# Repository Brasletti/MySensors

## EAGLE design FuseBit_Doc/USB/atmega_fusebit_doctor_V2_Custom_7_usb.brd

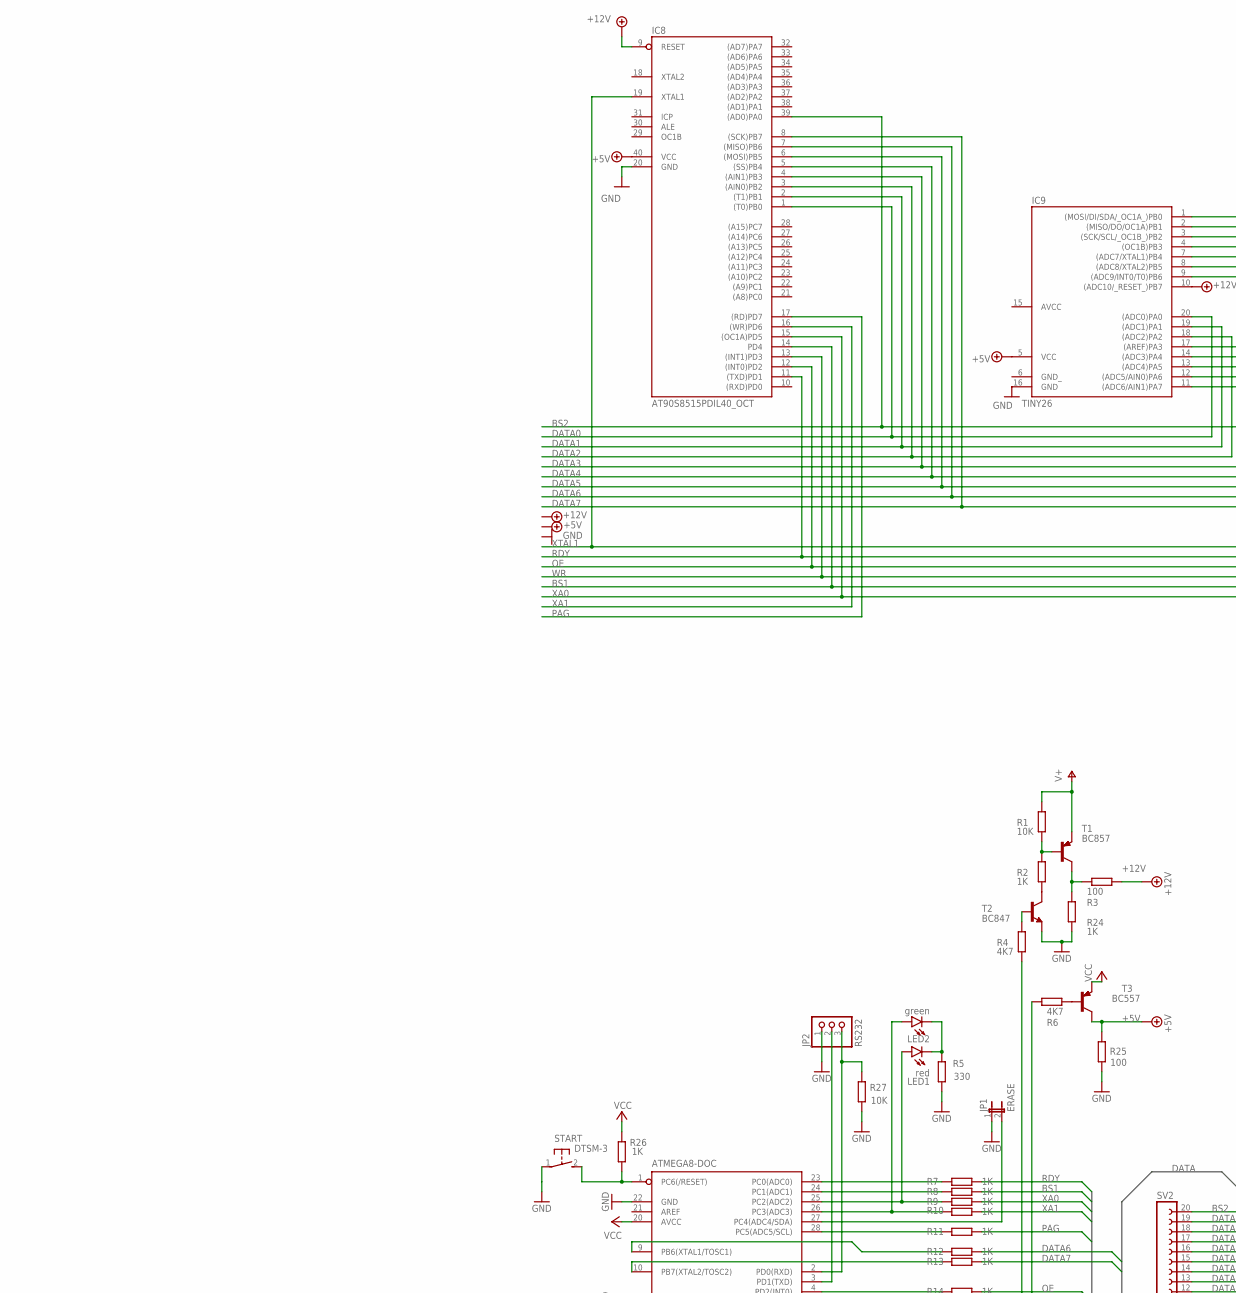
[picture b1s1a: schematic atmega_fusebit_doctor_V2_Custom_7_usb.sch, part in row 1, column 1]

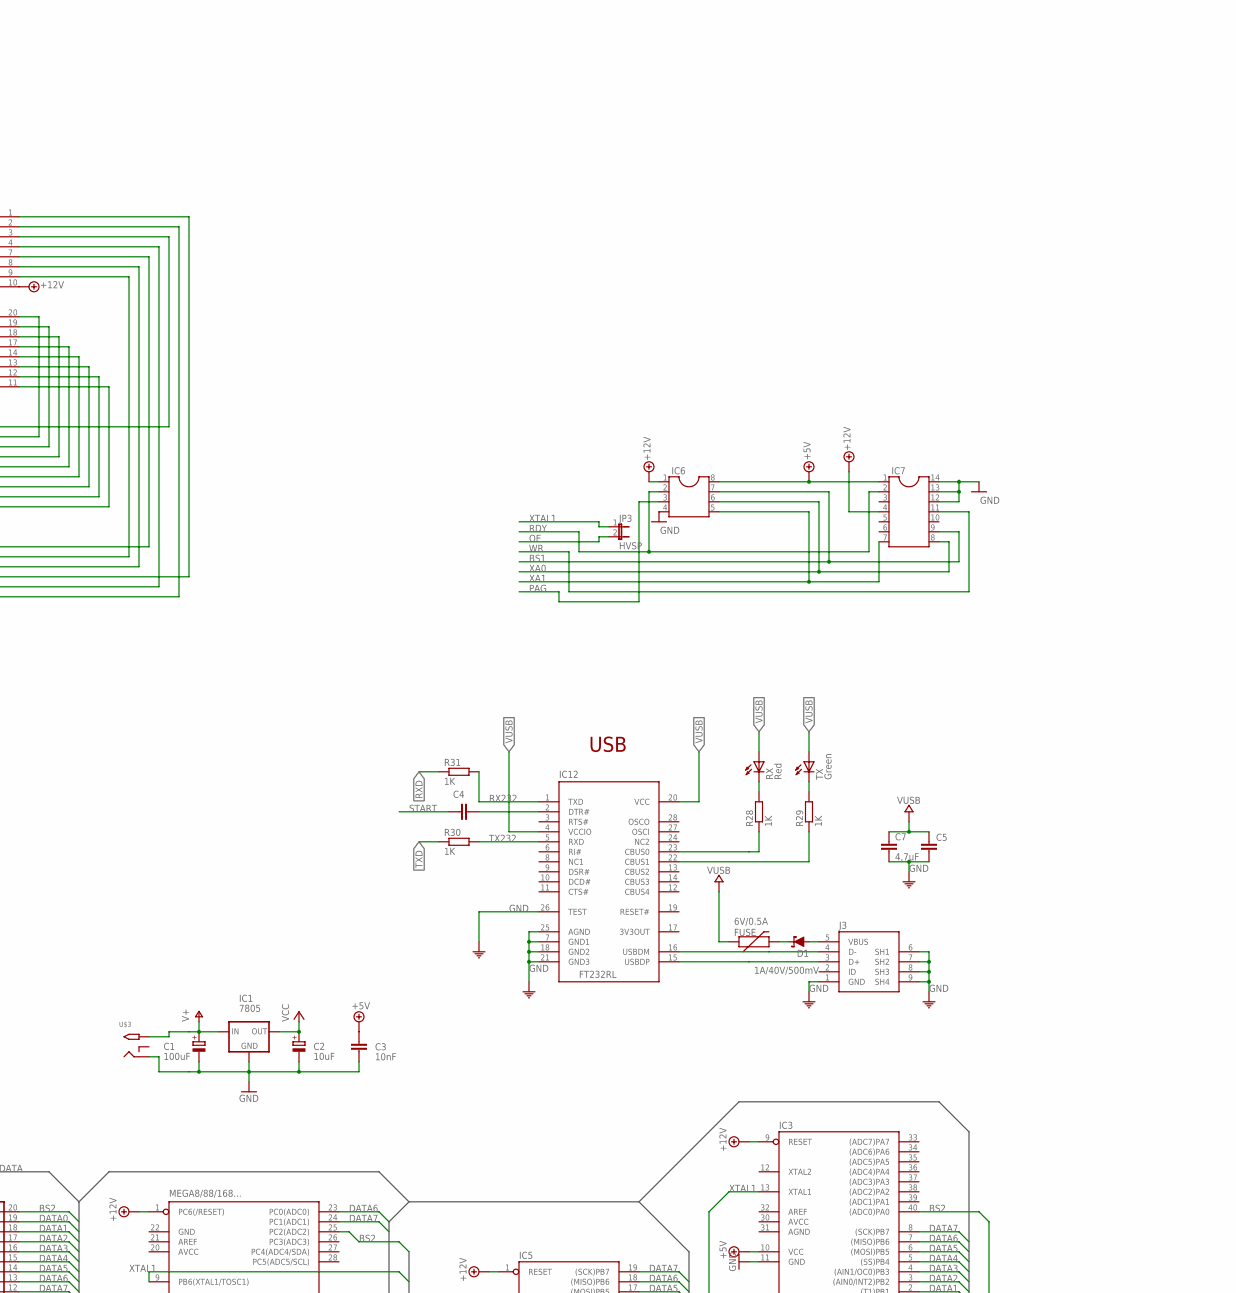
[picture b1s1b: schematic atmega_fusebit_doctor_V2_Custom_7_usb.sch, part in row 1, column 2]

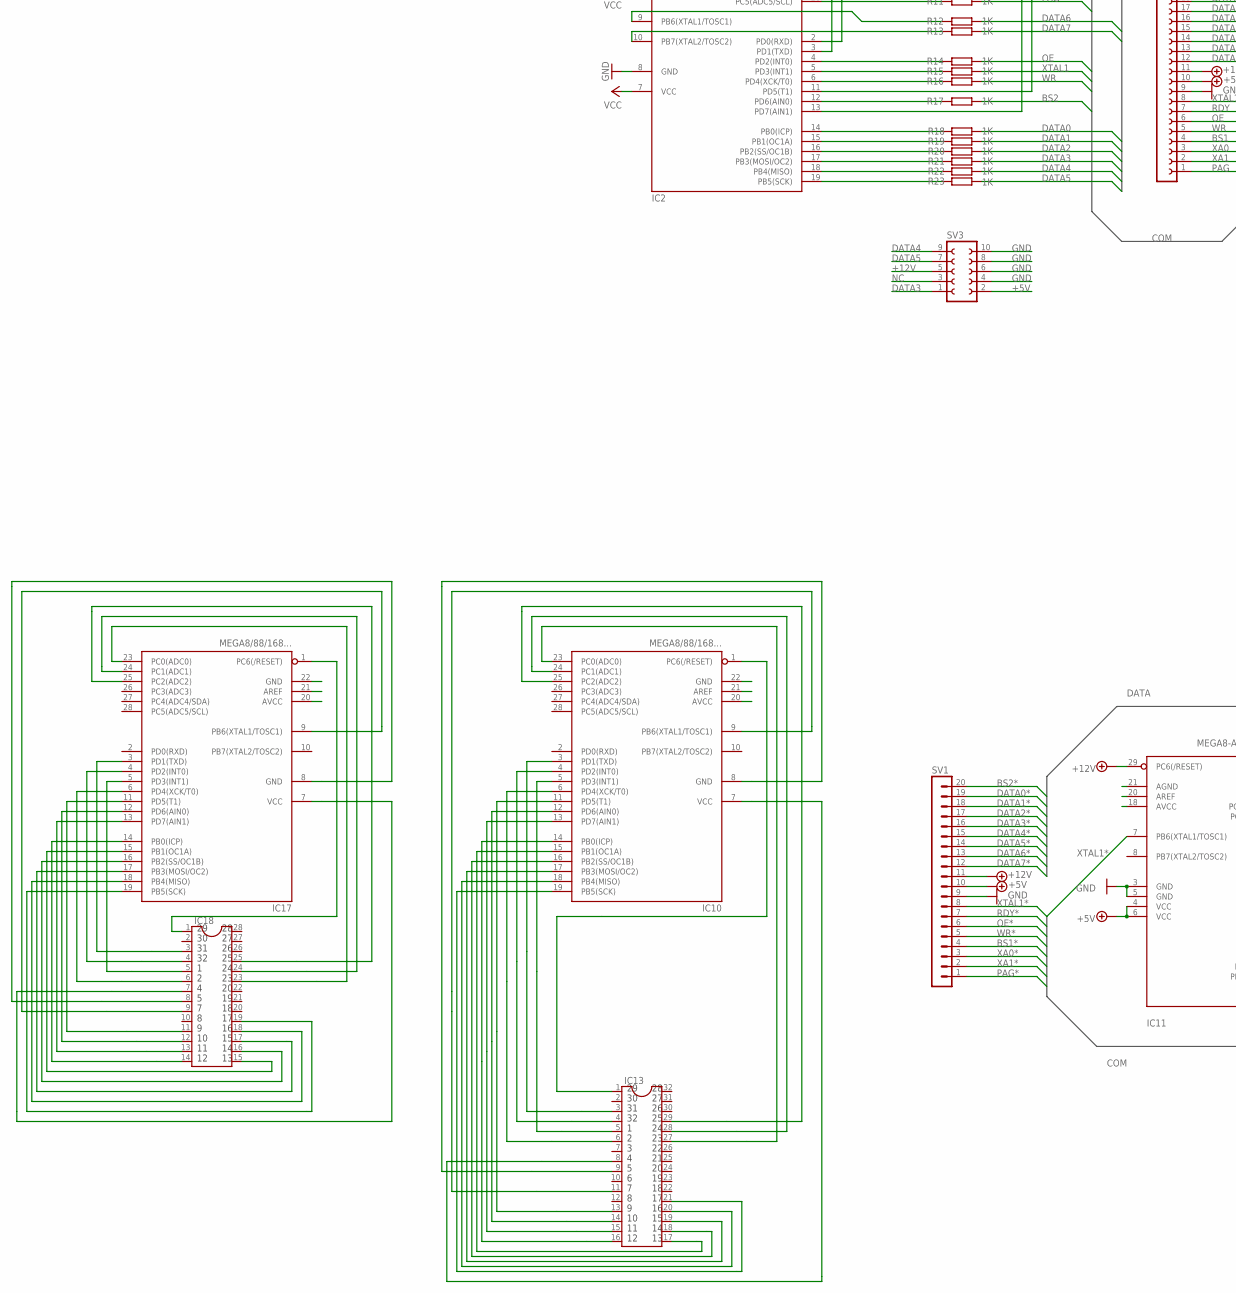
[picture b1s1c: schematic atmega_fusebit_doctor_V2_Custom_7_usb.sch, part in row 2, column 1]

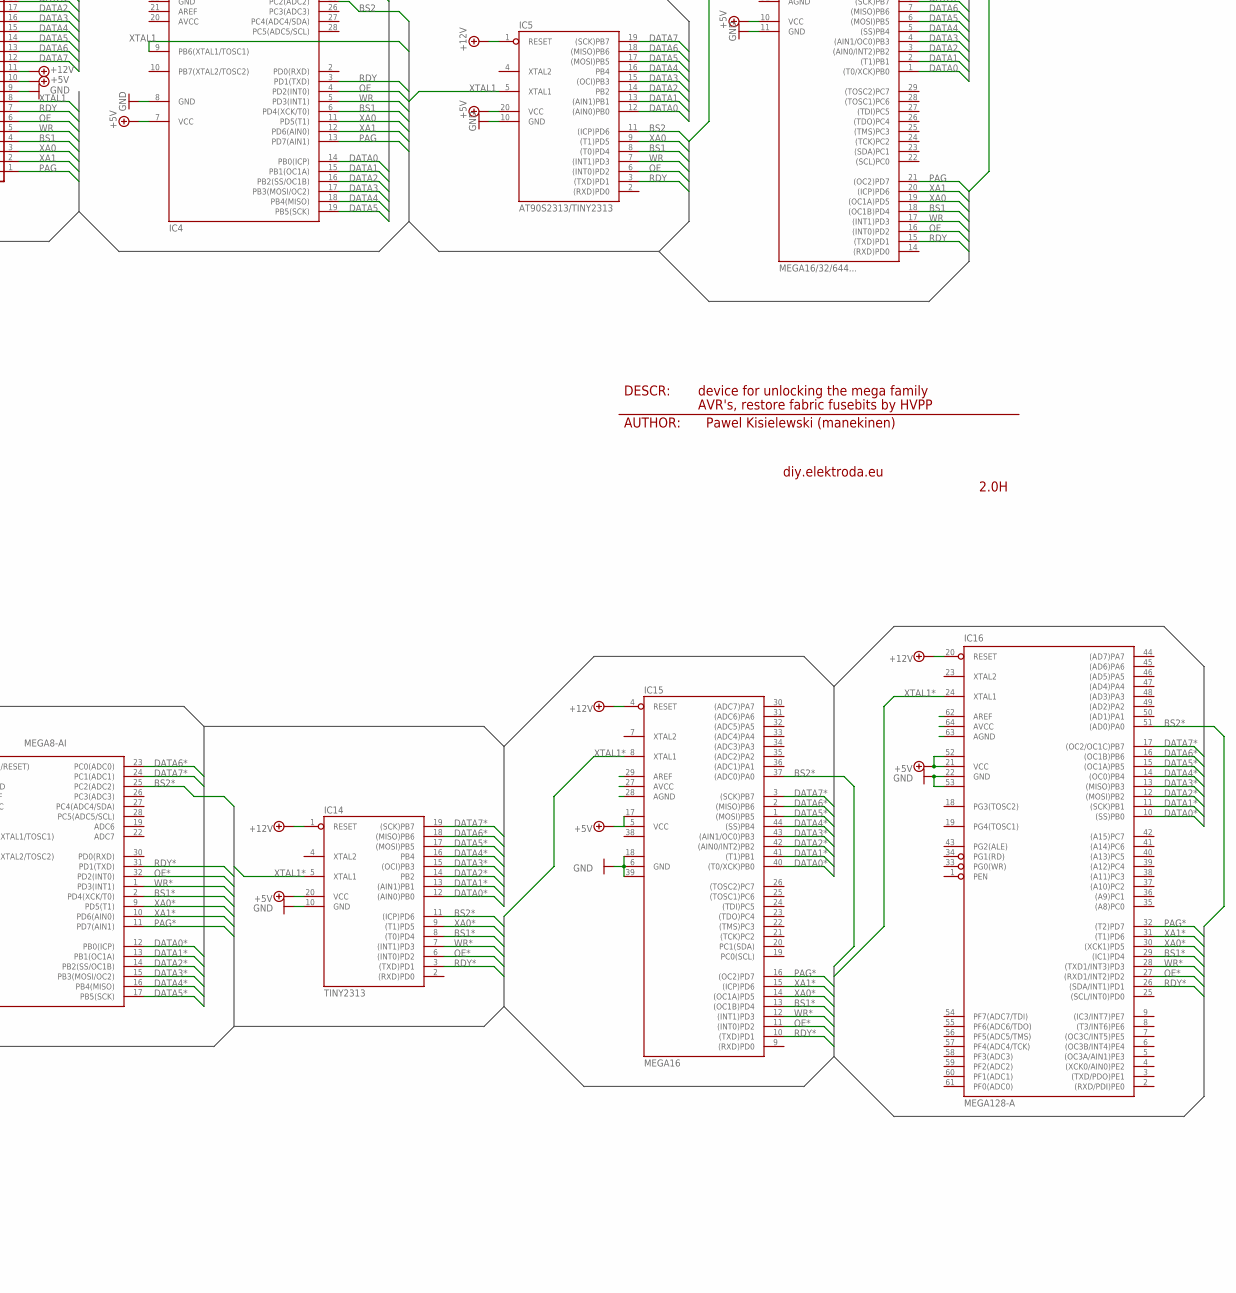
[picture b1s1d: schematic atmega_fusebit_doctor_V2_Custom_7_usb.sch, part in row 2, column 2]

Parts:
C1: 100uF; 153CLV-0605
C2: 10uF; 153CLV-0405
C3: 10nF; C0805
C4, C5: 100nF; C0805
C7: 4,7uF; C1206
D1: 1A/40V/500mV; SMA-DIODE
FUSE: 6V/0.5A; 1206
IC1: 7805; 78XXL
IC2: ATMEGA8-DOC; DIL28-3_OCT
IC3: MEGA16/32/644...; DIL40_OCT
IC4, IC10, IC17: MEGA8/88/168...; DIL28-3_OCT
IC5: AT90S2313/TINY2313; DIL20_OCT
IC6: DIL8S; SOCKED-08
IC7: DIL14S; SOCKED-14
IC8: AT90S8515PDIL40_OCT; DIL40_OCT
IC9: TINY26; DIL20_OCT
IC11: MEGA8-AI; TQFP32-08
IC12: FT232RL; SSOP28
IC13: DIL32
IC14: TINY2313; SO20L
IC15: MEGA16; TQFP44
IC16: MEGA128-A; TQFP64
IC18: DIL28; DIL28-6
J3: 0219_14850; USB-MINI-B_2
JP1: ERASE; JP1
JP2: RS232; 1X03
JP3: HVSP; JP1
LED1: red; LED-1206
LED2: green; LED-1206
R1, R27: 10K; R0805
R2, R7, R8, R9, R10, R11, R12, R13, R14, R15, R16, R17, R18, R19, R20, R21, R22, R23, R24, R26, R28, R29, R30, R31: 1K; R0805
R3, R25: 100; R0805
R4, R6: 4K7; R0805
R5: 330; R0805
RX: Red; CHIPLED_0805
START: DTSM-3
SV1: MA20-1
SV2: FE20-1; FE20
SV3: FE05-2
T1: BC857; SOT23-BEC
T2: BC847; SOT23
T3: BC557; SOT23-BEC
TX: Green; CHIPLED_0805
U$3: 2.1MMJACKTHM; PJ-102A

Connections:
1: IC10.5 (PD3(INT1)), IC13.5
2: IC10.6 (PD4(XCK/T0)), IC13.6
3: IC17.1 (PC6(/RESET)), IC18.1
3V3OUT: IC12.17 (3V3OUT)
4: IC10.7 (VCC), IC13.8
5: IC10.8 (GND), IC13.9
7: IC10.9 (PB6(XTAL1/TOSC1)), IC13.11
9: IC10.11 (PD5(T1)), IC13.13
10: IC10.12 (PD6(AIN0)), IC13.14
11: IC10.13 (PD7(AIN1)), IC13.15
12: IC10.14 (PB0(ICP)), IC13.16
13: IC10.15 (PB1(OC1A)), IC13.17
14: IC10.16 (PB2(SS/OC1B)), IC13.18
15: IC10.17 (PB3(MOSI/OC2)), IC13.19
16: IC10.18 (PB4(MISO)), IC13.20
17: IC10.19 (PB5(SCK)), IC13.21
19: IC17.3 (PD1(TXD)), IC18.3
20: IC17.4 (PD2(INT0)), IC18.4
21: IC17.5 (PD3(INT1)), IC18.5
22: IC17.6 (PD4(XCK/T0)), IC18.6
23: IC10.23 (PC0(ADC0)), IC13.27
24: IC10.24 (PC1(ADC1)), IC13.28
25: IC10.25 (PC2(ADC2)), IC13.29
29: IC10.1 (PC6(/RESET)), IC13.1
31: IC10.3 (PD1(TXD)), IC13.3
32: IC10.4 (PD2(INT0)), IC13.4
33: IC17.7 (VCC), IC18.7
34: IC17.8 (GND), IC18.8
35: IC17.9 (PB6(XTAL1/TOSC1)), IC18.9
37: IC17.11 (PD5(T1)), IC18.11
38: IC17.12 (PD6(AIN0)), IC18.12
39: IC17.13 (PD7(AIN1)), IC18.13
40: IC17.14 (PB0(ICP)), IC18.14
41: IC17.15 (PB1(OC1A)), IC18.15
42: IC17.16 (PB2(SS/OC1B)), IC18.16
43: IC17.17 (PB3(MOSI/OC2)), IC18.17
44: IC17.18 (PB4(MISO)), IC18.18
45: IC17.19 (PB5(SCK)), IC18.19
47: IC17.23 (PC0(ADC0)), IC18.23
48: IC17.24 (PC1(ADC1)), IC18.24
49: IC17.25 (PC2(ADC2)), IC18.25
+5V: C3.1, IC3.10 (VCC), IC4.7 (VCC), IC5.20 (VCC), IC6.8, IC7.1, IC8.40 (VCC), IC9.5 (VCC), R25.2, SV2.10, SV3.2, T3.C
+5V*: IC11.4 (VCC), IC11.6 (VCC), IC14.20 (VCC), IC15.5 (VCC), IC15.17 (VCC1), IC16.21 (VCC), IC16.52 (VCC1), SV1.10
+12V: IC3.9 (RESET), IC4.1 (PC6(/RESET)), IC5.1 (RESET), IC6.1, IC7.4, IC8.9 (RESET), IC9.10 ((ADC10/_RESET_)PB7), R3.2, SV2.11, SV3.5
+12V*: IC11.29 (PC6(/RESET)), IC14.1 (RESET), IC15.4 (RESET), IC16.20 (RESET), SV1.11
AGND: IC3.31 (AGND)
AREF: IC3.32 (AREF)
AVCC: IC3.30 (AVCC), IC4.20 (AVCC), IC9.15 (AVCC)
BS1: IC3.18 ((OC1B)PD4), IC4.6 (PD4(XCK/T0)), IC5.8 ((T0)PD4), IC6.7, IC7.9, IC8.14 (PD4), IC9.4 ((OC1B)PB3), R8.2, SV2.4
BS1*: IC11.2 (PD4(XCK/T0)), IC14.8 ((T0)PD4), IC15.13 ((OC1B)PD4), IC16.29 ((IC1)PD4), SV1.4
BS2: IC3.40 ((ADC0)PA0), IC4.25 (PC2(ADC2)), IC5.11 ((ICP)PD6), IC8.39 ((AD0)PA0), IC9.3 ((SCK/SCL/_OC1B_)PB2), R17.2, SV2.20
BS2*: IC11.25 (PC2(ADC2)), IC14.11 ((ICP)PD6), IC15.37 ((ADC0)PA0), IC16.51 ((AD0)PA0), SV1.20
DATA0: IC3.1 ((T0/XCK)PB0), IC4.14 (PB0(ICP)), IC5.12 ((AIN0)PB0), IC8.1 ((T0)PB0), IC9.20 ((ADC0)PA0), R18.2, SV2.19
DATA0*: IC11.12 (PB0(ICP)), IC14.12 ((AIN0)PB0), IC15.40 ((T0/XCK)PB0), IC16.10 ((SS)PB0), SV1.19
DATA1: IC3.2 ((T1)PB1), IC4.15 (PB1(OC1A)), IC5.13 ((AIN1)PB1), IC8.2 ((T1)PB1), IC9.19 ((ADC1)PA1), R19.2, SV2.18
DATA1*: IC11.13 (PB1(OC1A)), IC14.13 ((AIN1)PB1), IC15.41 ((T1)PB1), IC16.11 ((SCK)PB1), SV1.18
DATA2: IC3.3 ((AIN0/INT2)PB2), IC4.16 (PB2(SS/OC1B)), IC5.14 (PB2), IC8.3 ((AIN0)PB2), IC9.18 ((ADC2)PA2), R20.2, SV2.17
DATA2*: IC11.14 (PB2(SS/OC1B)), IC14.14 (PB2), IC15.42 ((AIN0/INT2)PB2), IC16.12 ((MOSI)PB2), SV1.17
DATA3: IC3.4 ((AIN1/OC0)PB3), IC4.17 (PB3(MOSI/OC2)), IC5.15 ((OCI)PB3), IC8.4 ((AIN1)PB3), IC9.17 ((AREF)PA3), R21.2, SV2.16, SV3.1
DATA3*: IC11.15 (PB3(MOSI/OC2)), IC14.15 ((OCI)PB3), IC15.43 ((AIN1/OC0)PB3), IC16.13 ((MISO)PB3), SV1.16
DATA4: IC3.5 ((SS)PB4), IC4.18 (PB4(MISO)), IC5.16 (PB4), IC8.5 ((SS)PB4), IC9.14 ((ADC3)PA4), R22.2, SV2.15, SV3.9
DATA4*: IC11.16 (PB4(MISO)), IC14.16 (PB4), IC15.44 ((SS)PB4), IC16.14 ((OC0)PB4), SV1.15
DATA5: IC3.6 ((MOSI)PB5), IC4.19 (PB5(SCK)), IC5.17 ((MOSI)PB5), IC8.6 ((MOSI)PB5), IC9.13 ((ADC4)PA5), R23.2, SV2.14, SV3.7
DATA5*: IC11.17 (PB5(SCK)), IC14.17 ((MOSI)PB5), IC15.1 ((MOSI)PB5), IC16.15 ((OC1A)PB5), SV1.14
DATA6: IC3.7 ((MISO)PB6), IC4.23 (PC0(ADC0)), IC5.18 ((MISO)PB6), IC8.7 ((MISO)PB6), IC9.12 ((ADC5/AIN0)PA6), R12.2, SV2.13
DATA6*: IC11.23 (PC0(ADC0)), IC14.18 ((MISO)PB6), IC15.2 ((MISO)PB6), IC16.16 ((OC1B)PB6), SV1.13
DATA7: IC3.8 ((SCK)PB7), IC4.24 (PC1(ADC1)), IC5.19 ((SCK)PB7), IC8.8 ((SCK)PB7), IC9.11 ((ADC6/AIN1)PA7), R13.2, SV2.12
DATA7*: IC11.24 (PC1(ADC1)), IC14.19 ((SCK)PB7), IC15.3 ((SCK)PB7), IC16.17 ((OC2/OC1C)PB7), SV1.12
GND: C1.-, C2.-, C3.2, C5.2, C7.2, IC1.GND, IC2.8 (GND), IC2.22 (GND), IC3.11 (GND), IC4.8 (GND), IC4.22 (GND), IC5.10 (GND), IC6.4, IC7.12, IC7.13, IC7.14, IC8.20 (GND), IC9.16 (GND), IC12.7 (GND1), IC12.18 (GND2), IC12.21 (GND3), IC12.25 (AGND), IC12.26 (TEST), J3.1 (GND), J3.6 (SH1), J3.7 (SH2), J3.8 (SH3), J3.9 (SH4), JP1.1, JP2.1, R5.1, R24.1, R25.1, R27.2, START.1, SV2.9, SV3.4, SV3.6, SV3.8, SV3.10, T2.2 (E), U$3.RING
GND*: IC11.3 (GND), IC11.5 (GND), IC14.10 (GND), IC15.6 (GND), IC15.18 (GND1), IC15.39 (GND2), IC16.22 (GND), IC16.53 (GND1), SV1.9
GND_: IC9.6 (GND_)
unnamed: R6.1, T3.B
unnamed: IC2.14 (PB0(ICP)), R18.1
unnamed: IC2.28 (PC5(ADC5/SCL)), R11.1
unnamed: IC2.6 (PD4(XCK/T0)), R16.1
unnamed: IC2.4 (PD2(INT0)), R14.1
unnamed: R2.2, T2.3 (C)
unnamed: IC2.9 (PB6(XTAL1/TOSC1)), R12.1
unnamed: IC2.10 (PB7(XTAL2/TOSC2)), R13.1
unnamed: IC2.13 (PD7(AIN1)), R4.2
unnamed: IC2.11 (PD5(T1)), R6.2
unnamed: IC2.15 (PB1(OC1A)), R19.1
unnamed: IC2.16 (PB2(SS/OC1B)), R20.1
unnamed: IC2.5 (PD3(INT1)), R15.1
unnamed: IC2.23 (PC0(ADC0)), R7.1
unnamed: R3.1, R24.2, T1.C
unnamed: IC2.17 (PB3(MOSI/OC2)), R21.1
unnamed: IC2.18 (PB4(MISO)), R22.1
unnamed: IC2.19 (PB5(SCK)), R23.1
unnamed: IC2.12 (PD6(AIN0)), R17.1
unnamed: R4.1, T2.1 (B)
unnamed: IC2.27 (PC4(ADC4/SDA)), JP1.2
unnamed: LED1.C, LED2.C, R5.2
unnamed: R1.2, R2.1, T1.B
unnamed: C4.2, IC12.2 (DTR#)
unnamed: IC2.24 (PC1(ADC1)), R8.1
unnamed: IC12.15 (USBDP), J3.3 (D+)
unnamed: IC12.16 (USBDM), J3.4 (D-)
unnamed: IC12.23 (CBUS0), R28.1
unnamed: IC2.26 (PC3(ADC3)), LED2.A, R10.1
unnamed: IC2.25 (PC2(ADC2)), LED1.A, R9.1
unnamed: IC12.22 (CBUS1), R29.1
unnamed: R28.2, RX.C
unnamed: R29.2, TX.C
NC: SV3.3
OE: IC3.16 ((INT0)PD2), IC4.4 (PD2(INT0)), IC5.6 ((INT0)PD2), IC8.12 ((INT0)PD2), IC9.8 ((ADC8/XTAL2)PB5), JP3.2, R14.2, SV2.6
OE*: IC11.32 (PD2(INT0)), IC14.6 ((INT0)PD2), IC15.11 ((INT0)PD2), IC16.27 ((RXD1/INT2)PD2), SV1.6
PAG: IC3.21 ((OC2)PD7), IC4.13 (PD7(AIN1)), IC6.3, IC8.17 ((RD)PD7), R11.2, SV2.1
PAG*: IC11.11 (PD7(AIN1)), IC15.16 ((OC2)PD7), IC16.32 ((T2)PD7), SV1.1
RDY: IC3.15 ((TXD)PD1), IC4.3 (PD1(TXD)), IC5.3 ((TXD)PD1), IC6.2, IC7.2, IC8.11 ((TXD)PD1), IC9.9 ((ADC9/INT0/T0)PB6), R7.2, SV2.7
RDY*: IC11.31 (PD1(TXD)), IC14.3 ((TXD)PD1), IC15.10 ((TXD)PD1), IC16.26 ((SDA/INT1)PD1), SV1.7
RX232: IC12.1 (TXD), R31.2
RXD: IC2.2 (PD0(RXD)), JP2.3, R27.1, R31.1
START: C4.1, IC2.1 (PC6(/RESET)), R26.1, START.2
TX232: IC12.5 (RXD), R30.2
TXD: IC2.3 (PD1(TXD)), JP2.2, R30.1
V+: C1.+, IC1.IN, R1.1, T1.E, U$3.TIP
VCC: C2.+, IC1.OUT, IC2.7 (VCC), IC2.20 (AVCC), R26.2, T3.E
VCC2: IC15.38 (VCC2)
VUSB: C5.1, C7.1, FUSE.1, IC12.4 (VCCIO), IC12.20 (VCC), RX.A, TX.A
VUSB_PREFUSE: D1.C, FUSE.2
VUSB_RAW: D1.A, J3.5 (VBUS)
WR: IC3.17 ((INT1)PD3), IC4.5 (PD3(INT1)), IC5.7 ((INT1)PD3), IC7.11, IC8.13 ((INT1)PD3), IC9.1 ((MOSI/DI/SDA/_OC1A_)PB0), R16.2, SV2.5
WR*: IC11.1 (PD3(INT1)), IC14.7 ((INT1)PD3), IC15.12 ((INT1)PD3), IC16.28 ((TXD1/INT3)PD3), SV1.5
XA0: IC3.19 ((OC1A)PD5), IC4.11 (PD5(T1)), IC5.9 ((T1)PD5), IC6.6, IC7.8, IC8.15 ((OC1A)PD5), IC9.2 ((MISO/DO/OC1A)PB1), R9.2, SV2.3
XA0*: IC11.9 (PD5(T1)), IC14.9 ((T1)PD5), IC15.14 ((OC1A)PD5), IC16.30 ((XCK1)PD5), SV1.3
XA1: IC3.20 ((ICP)PD6), IC4.12 (PD6(AIN0)), IC6.5, IC7.7, IC8.16 ((WR)PD6), R10.2, SV2.2
XA1*: IC11.10 (PD6(AIN0)), IC15.15 ((ICP)PD6), IC16.31 ((T1)PD6), SV1.2
XTAL1: IC3.13 (XTAL1), IC4.9 (PB6(XTAL1/TOSC1)), IC5.5 (XTAL1), IC8.19 (XTAL1), IC9.7 ((ADC7/XTAL1)PB4), JP3.1, R15.2, SV2.8
XTAL1*: IC11.7 (PB6(XTAL1/TOSC1)), IC14.5 (XTAL1), IC15.8 (XTAL1), IC16.24 (XTAL1), SV1.8

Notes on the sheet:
AUTHOR:
DESCR:
device for unlocking the mega family
AVR's, restore fabric fusebits by HVPP
Pawel Kisielewski (manekinen)
2.0H
diy.elektroda.eu
USB

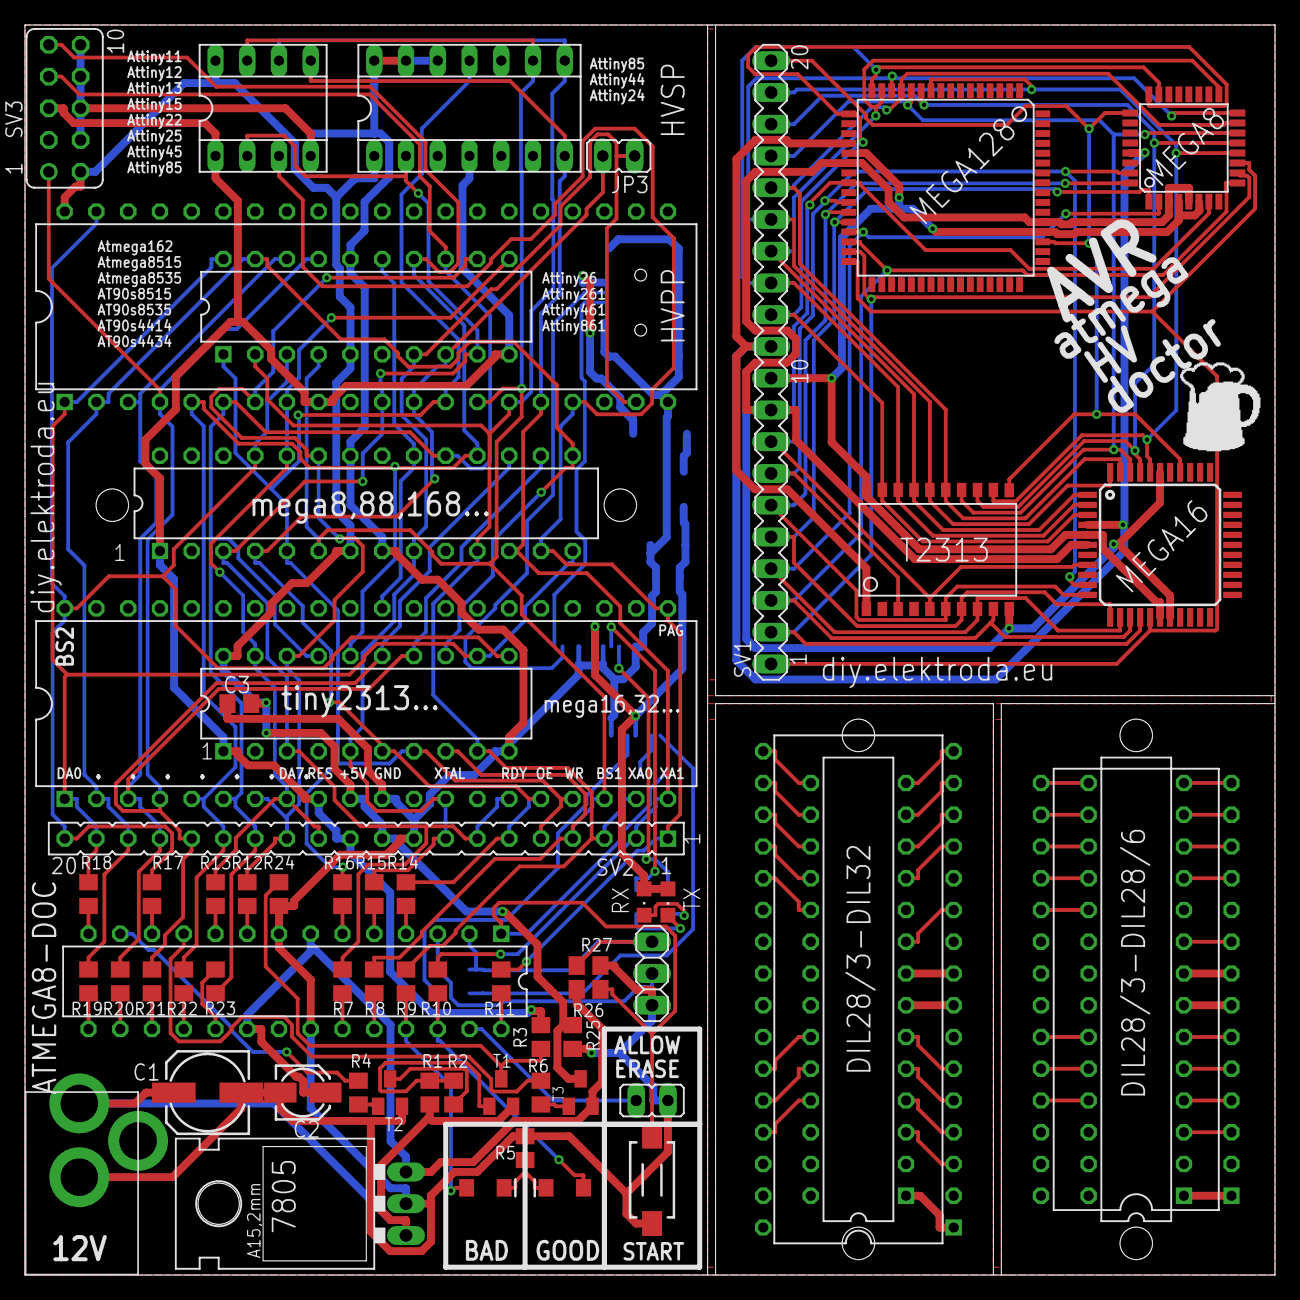
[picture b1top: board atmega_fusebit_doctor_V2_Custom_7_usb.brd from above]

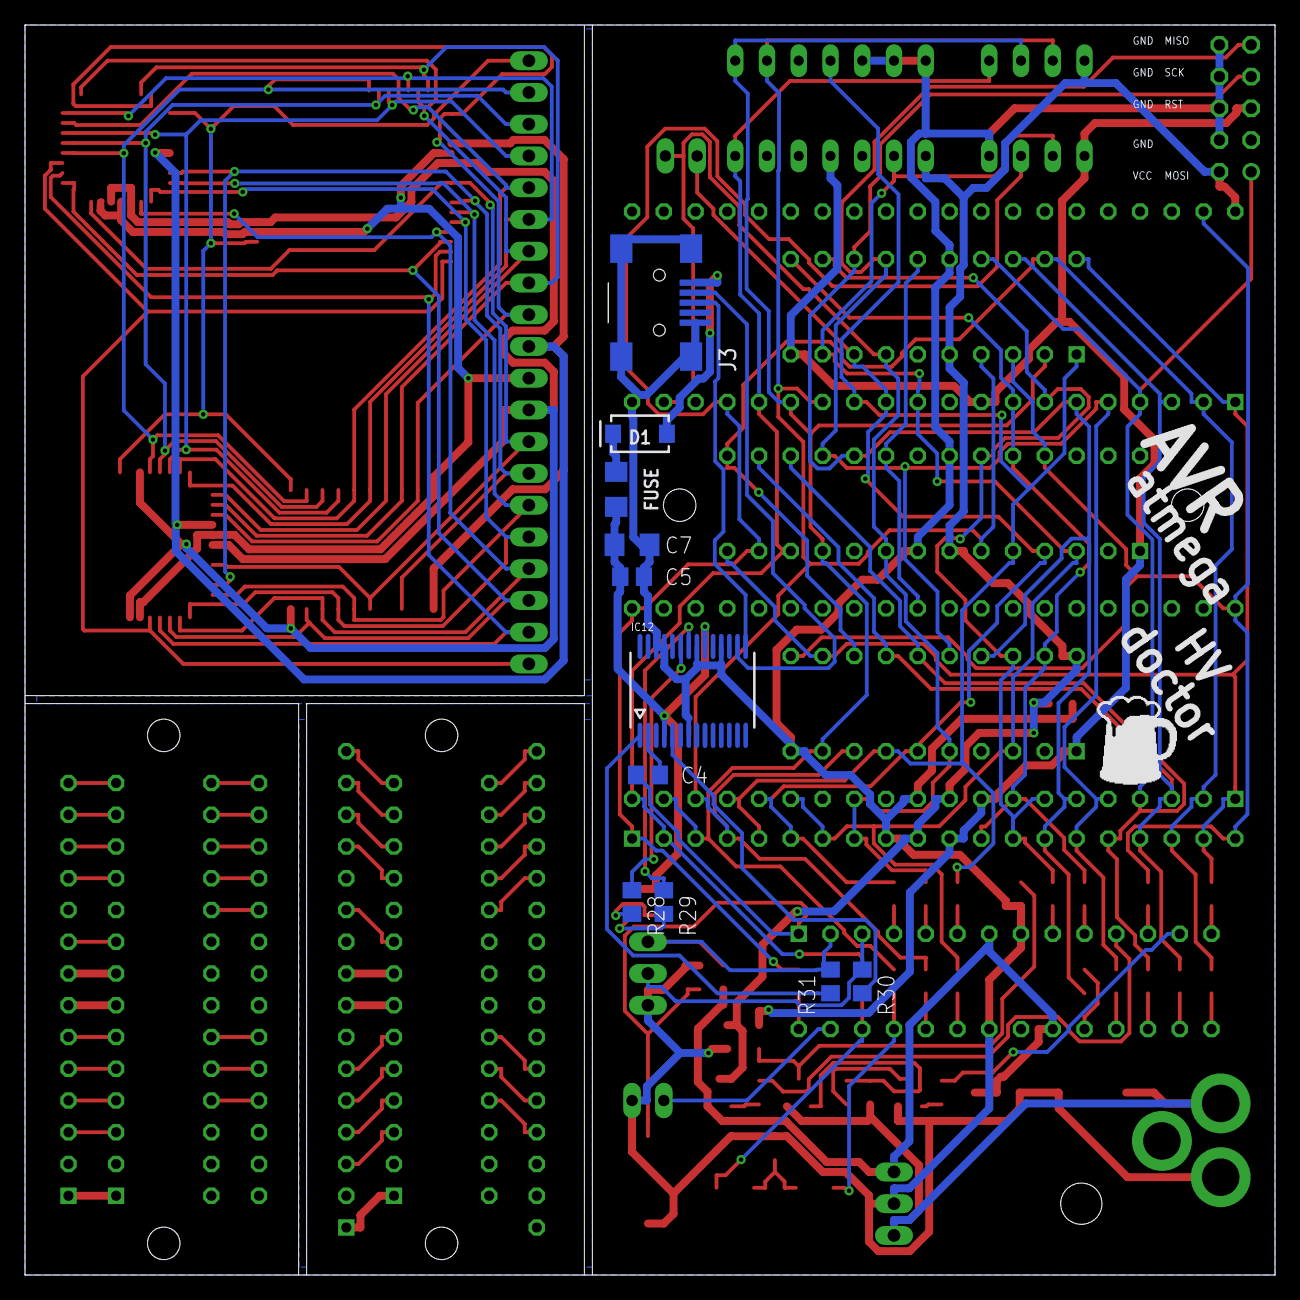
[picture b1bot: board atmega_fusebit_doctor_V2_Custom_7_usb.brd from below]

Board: 2 copper layers, 100.0 x 100.0 mm, 73 parts (11 on the bottom side), 124 nets.

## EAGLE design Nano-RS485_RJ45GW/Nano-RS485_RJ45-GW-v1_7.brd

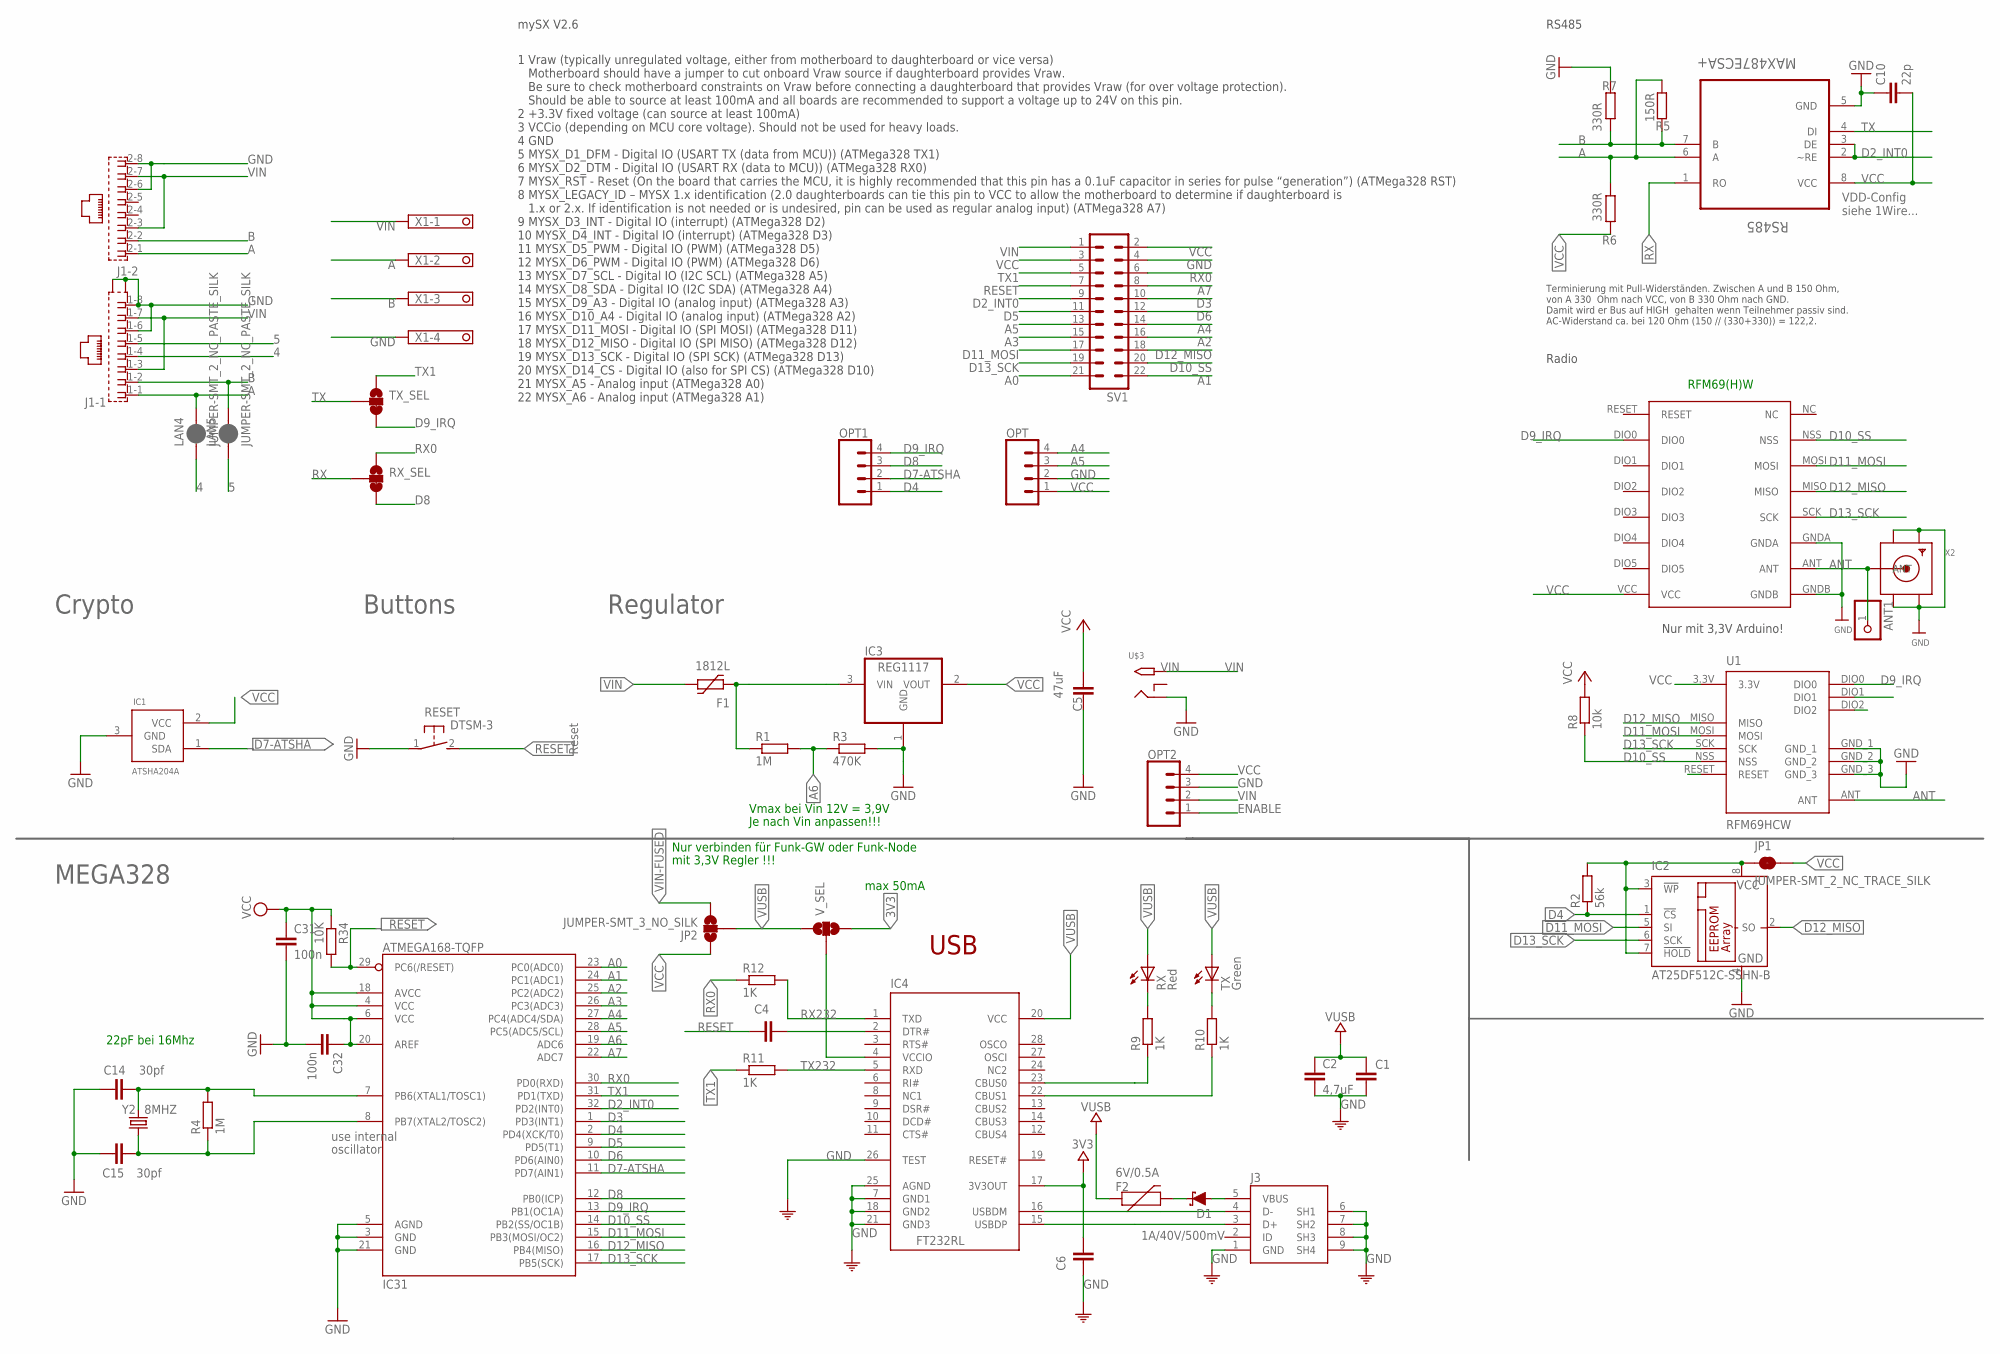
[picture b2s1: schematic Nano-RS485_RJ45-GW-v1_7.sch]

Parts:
ANT1: PINHD-1X1; 1X01
C1, C4, C6: 100nF; C0805
C2: 4,7uF; C1206
C5: 47uF; C1206
C10: 22p; C0805
C14, C15: 30pf; 0805
C31, C32: 100n; C0805
D1: 1A/40V/500mV; SMA-DIODE
F1: 1812L
F2: 6V/0.5A; 1206
IC1: ATSHA204A; SOT23
IC2: AT25DF512C-SSHN-B; SO-08
IC3: REG1117; SOT223
IC4: FT232RL; SSOP28
IC31: ATMEGA168-TQFP; TQFP32-08
J1: RJ45_2X_NARROW_SHILDPINS_NOCASE
J3: 0219_14850; USB-MINI-B_2
JP1: JUMPER-SMT_2_NC_TRACE_SILK; SMT-JUMPER_2_NC_TRACE_SILK
JP2: JUMPER-SMT_3_NO_SILK; SMT-JUMPER_3_NO_SILK
LAN4, LAN5: JUMPER-SMT_2_NC_PASTE_SILK; SMT-JUMPER_2_NC_PASTE_SILK
OPT, OPT1, OPT2: CONN_04; 1X04
R1, R4: 1M; M0805
R2: 56k; M0805
R3: 470K; R0805
R5: 150R; R0805
R6, R7: 330R; R0805
R8: 10k; M0805
R9, R10, R11, R12: 1K; R0805
R34: 10K; R0805
RESET: DTSM-3
RFM69W: RFM69HW; RFM
RS485: MAX487ECSA+; SOIC127P600X175-8N
RX: Red; CHIPLED_0805
RX_SEL: JUMPER-SMT_3_1-NC_TRACE_SILK; SMT-JUMPER_3_1-NC_TRACE_SILK
SV1: MA11-2
TX: Green; CHIPLED_0805
TX_SEL: JUMPER-SMT_3_1-NC_TRACE_SILK; SMT-JUMPER_3_1-NC_TRACE_SILK
U1: RFM69HCW; RFM69HCW-XXXS2
U$3: 2.1MMJACKTHM; PJ-102A
V_SEL: JUMPER-SMT_3_NO_SILK; SMT-JUMPER_3_NO_SILK
X1: 1751264
X2: SMACONNECTOR_EDGE; SMA_EDGELAUNCH
Y2: 8MHZ; CRYSTAL-TXC-7A

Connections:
3V3: C6.2, IC4.17 (3V3OUT), V_SEL.3
4: J1.1-4 (4), LAN4.1
5: J1.1-5 (5), LAN5.1
A: J1.1-1 (1), J1.2-1 (1), LAN4.2, R5.1, R6.2, RS485.6 (A), X1.2
A0: IC31.23 (PC0(ADC0)), SV1.21
A1: IC31.24 (PC1(ADC1)), SV1.22
A2: IC31.25 (PC2(ADC2)), SV1.16
A3: IC31.26 (PC3(ADC3)), SV1.15
A4: IC31.27 (PC4(ADC4/SDA)), OPT.4, SV1.14
A5: IC31.28 (PC5(ADC5/SCL)), OPT.3, SV1.13
A6: IC31.19 (ADC6), R1.2, R3.1
A7: IC31.22 (ADC7), SV1.8
ANT: ANT1.1, RFM69W.ANT, U1.ANT, X2.P (ANT)
B: J1.1-2 (2), J1.2-2 (2), LAN5.2, R5.2, R7.1, RS485.7 (B), X1.3
D2_INT0: IC31.32 (PD2(INT0)), RS485.2 (~RE), RS485.3 (DE), SV1.9
D3: IC31.1 (PD3(INT1)), SV1.10
D4: IC2.1 (!CS), IC31.2 (PD4(XCK/T0)), OPT1.1, R2.1
D5: IC31.9 (PD5(T1)), SV1.11
D6: IC31.10 (PD6(AIN0)), SV1.12
D7-ATSHA: IC1.1 (SDA), IC31.11 (PD7(AIN1)), OPT1.2
D8: IC31.12 (PB0(ICP)), OPT1.3, RX_SEL.3
D9_IRQ: IC31.13 (PB1(OC1A)), OPT1.4, RFM69W.DIO0, TX_SEL.3, U1.DIO0
D10_SS: IC31.14 (PB2(SS/OC1B)), R8.1, RFM69W.NSS, SV1.20, U1.NSS
D11_MOSI: IC2.5 (SI), IC31.15 (PB3(MOSI/OC2)), RFM69W.MOSI, SV1.17, U1.MOSI
D12_MISO: IC2.2 (SO), IC31.16 (PB4(MISO)), RFM69W.MISO, SV1.18, U1.MISO
D13_SCK: IC2.6 (SCK), IC31.17 (PB5(SCK)), RFM69W.SCK, SV1.19, U1.SCK
ENABLE: OPT2.1
GND: C1.2, C2.2, C5.1, C6.1, C10.1, C14.1, C15.1, C31.2, C32.2, IC1.3 (GND), IC2.4 (GND), IC3.1 (GND), IC4.7 (GND1), IC4.18 (GND2), IC4.21 (GND3), IC4.25 (AGND), IC4.26 (TEST), IC31.3 (GND), IC31.5 (AGND), IC31.21 (GND), J1.1-6 (6), J1.1-8 (8), J1.2-6 (6), J1.2-8 (8), J1.G1 (S1), J1.G3 (S2), J3.1 (GND), J3.6 (SH1), J3.7 (SH2), J3.8 (SH3), J3.9 (SH4), OPT.2, OPT2.3, R3.2, R7.2, RESET.1, RFM69W.GNDA, RFM69W.GNDB, RS485.5 (GND), SV1.4, U1.GND_1, U1.GND_2, U1.GND_3, U$3.RING, X1.4, X2.GND@1 (GND4), X2.GND@2 (GND3), X2.GND@3 (GND2), X2.GND@4 (GND1)
unnamed: IC4.4 (VCCIO), V_SEL.2
unnamed: IC4.22 (CBUS1), R10.1
unnamed: C14.2, IC31.7 (PB6(XTAL1/TOSC1)), R4.2, Y2.P$2 (2)
unnamed: C4.2, IC4.2 (DTR#)
unnamed: IC4.15 (USBDP), J3.3 (D+)
unnamed: IC4.16 (USBDM), J3.4 (D-)
unnamed: R9.2, RX.C
unnamed: IC4.23 (CBUS0), R9.1
unnamed: R10.2, TX.C
unnamed: C15.2, IC31.8 (PB7(XTAL2/TOSC2)), R4.1, Y2.P$1 (1)
RESET: C4.1, IC31.29 (PC6(/RESET)), R34.2, RESET.2, SV1.7
RX: RS485.1 (RO), RX_SEL.2
RX0: IC31.30 (PD0(RXD)), R12.1, RX_SEL.1, SV1.6
RX232: IC4.1 (TXD), R12.2
TX: RS485.4 (DI), TX_SEL.2
TX1: IC31.31 (PD1(TXD)), R11.1, SV1.5, TX_SEL.1
TX232: IC4.5 (RXD), R11.2
VCC: C5.2, C10.2, C31.1, C32.1, IC1.2 (VCC), IC3.2 (VOUT), IC31.4 (VCC), IC31.6 (VCC), IC31.18 (AVCC), IC31.20 (AREF), JP1.2, JP2.1, OPT.1, OPT2.4, R6.1, R8.2, R34.1, RFM69W.VCC, RS485.8 (VCC), SV1.2, SV1.3, U1.3.3V
VCC1: IC2.3 (!WP), IC2.7 (!HOLD), IC2.8 (VCC), JP1.1, R2.2
VIN: F1.P$2 (2), J1.1-3 (3), J1.1-7 (7), J1.2-3 (3), J1.2-7 (7), OPT2.2, SV1.1, U$3.TIP, X1.1
VIN-FUSED: F1.P$1 (1), IC3.3 (VIN), JP2.3, R1.1
VUSB: C1.1, C2.1, F2.1, IC4.20 (VCC), JP2.2, RX.A, TX.A, V_SEL.1
VUSB_PREFUSE: D1.C, F2.2
VUSB_RAW: D1.A, J3.5 (VBUS)

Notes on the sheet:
MEGA328
use internal
oscillator
Reset
Crypto
Buttons
Regulator
RS485
VDD-Config siehe 1Wire...
Terminierung mit Pull-Widerständen. Zwischen A und B 150 Ohm, von A 330 Ohm nach VCC, von B 330 Ohm nach GND. Damit wird er Bus auf HIGH gehalten wenn Teilnehmer passiv sind. AC-Widerstand ca. bei 120 Ohm (150 // (330+330)) = 122,2.
1 Vraw (typically unregulated voltage, either from motherboard to daughterboard or vice versa) Motherboard should have a jumper to cut onboard Vraw source if daughterboard provides Vraw. Be sure to check motherboard constraints on Vraw before connecting a daughterboard that provides Vraw (for over 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
mySX V2.6
RFM69(H)W
Nur mit 3,3V Arduino!
Radio
USB
22pF bei 16Mhz
Vmax bei Vin 12V = 3,9V
max 50mA
mit 3,3V Regler !!!
Nur verbinden für Funk-GW oder Funk-Node
Je nach Vin anpassen!!!

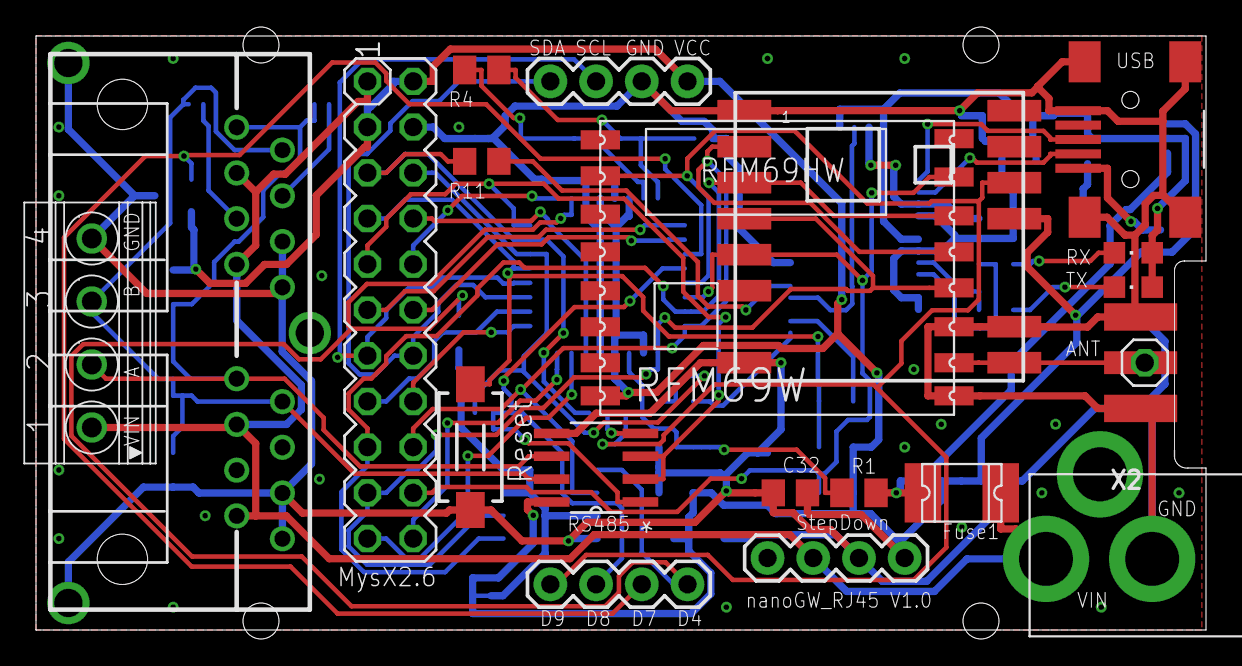
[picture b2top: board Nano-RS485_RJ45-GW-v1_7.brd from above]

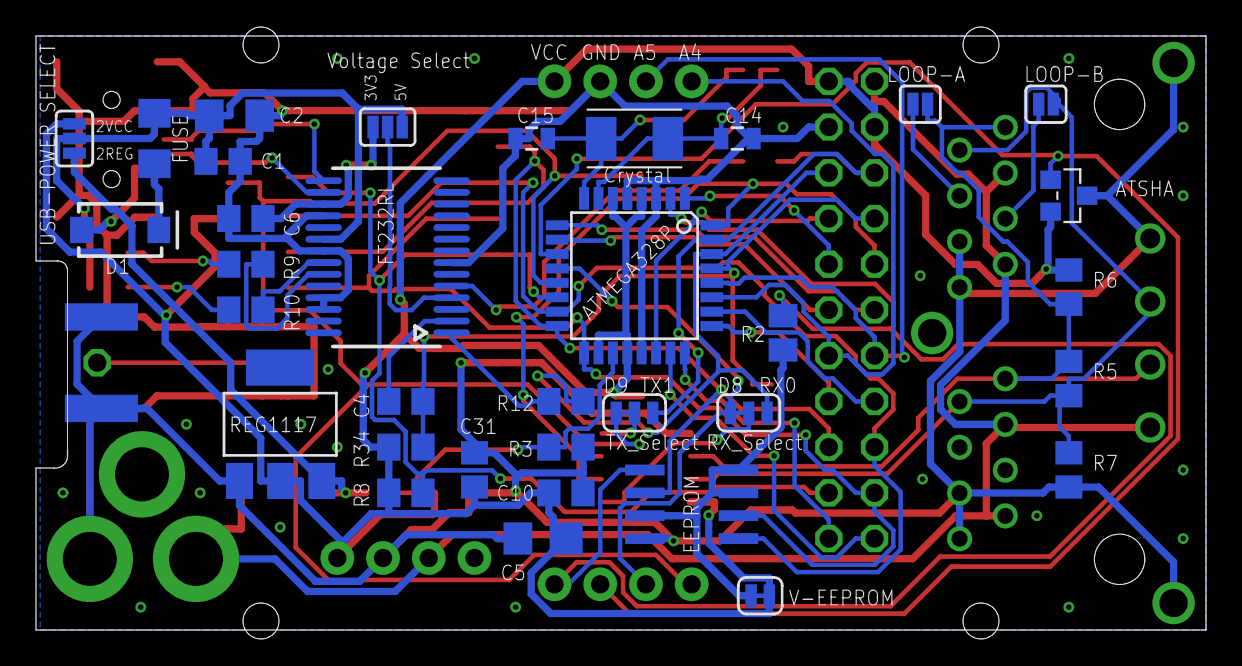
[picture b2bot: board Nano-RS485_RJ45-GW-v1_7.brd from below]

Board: 2 copper layers, 65.0 x 33.0 mm, 55 parts (34 on the bottom side), 51 nets.

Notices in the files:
parts and their libraries:
SparkFun-LED: Licensing: Creative Commons ShareAlike 4.0 International - https://creativecommons.org/licenses/by-sa/4.0
SparkFun-Aesthetics: Licensing: CC v3.0 Share-Alike You are welcome to use this library for commercial purposes.
